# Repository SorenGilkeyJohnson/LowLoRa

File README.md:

# Low Power LoRa Weather Station

A solar powered, batteryless LoRa (expandable) sensor node powered from a supercapacitor charged by a small solar cell using an energy harvester. This was built around the Semtech SX1262 LoRa transceiver (US band; 915 MHz) and the low power MSPM0L110x MCU (TI; M0+), this board is a monitoring platform for anything you might want! The board is made around the solar cell and is roughly 23x24mm. 

## Overview

When researching this concept, I had found a few previous examples of this being done (e.g. [nootropicdesign](hackster.io/nootropicdesign/solar-powered-lora-weather-station-36b6ea)). I had not found an example, however, of a board that was fully self contained. When I was researching the component selection I really wanted it to be fully on board, which drove my decision to use a supercapacitor over a traditional Li-ION cell (almost none are SMD) and made me want to use a chip or PCB antenna. I found a supercapacitor that should work (this is my first time working with them), but I did not have enough room for an onboard antenna. Because of this I decided to add an external antenna through a connector. Another reason for this is the solar cell can block the RF waves from propagating properly. My project is still fairly unique from any existing solution, because I have found that it is rare to use a SMD solar cell. This is one of the biggest ones available on the market, as most are designed for handheld calculators. 
    Figuring out the power budget was very difficult for this project, and that was probably the thing I spent the most time on. Thankfully, the SX1262 datasheet had detailed power budget options, and I was able to base it off of that (almost all of my battery consumption should be from that). This project taught me a lot about the importance of component selection! (I probably spent 2 times longer on this than any other project I had done vs the routing). 
    When I get the board, I hope I can get it so that it is watertight. I have already done some research into gaskets for the humidity sensor (as this needs access to the outside world to get a good reading), but this seems pretty hard to do. There is a version of the sensor that has this built in, but it is far more expensive and is hard to get from most suppliers. I plan to use silicone around the PCB to protect the border of the solar cell from accidental damage, and put a piece of fiberglass over it. I made sure to keep all the parts that would petrude together, so I should have a slightly easier time designing the case. I hope I can get this board and test it out soon!

## Key Features

* **Ultra Low Power** This PCB should run at ultra low power, and may be able to run continuously in good sunlight (although it is designed for far less).
* **Small Board Size** The board for this is quite compact, and is mainly constrained by the size of the solar cell.
* **LoRa Transmit** This should be able to transfer over very long distances, and should be able to also extend range of other forming a "mesh"
* **Future expansion** Plentiful GPIO pins are broken out, so if one wanted to add more sensors, it would be as easy as soldering additional connectors to the PCB test pads.

## How It Works

1. The solar cell charges a supercapacitor through the BQ25504 energy harvesting IC, which is designed to extract power efficiently over a long period of time from very low amperage power sources. The datasheet mentioned being able to charge off of a piezoelectric element which would be way under the amount of current generated by a solar cell. Hopefully, this will overcome the natural discharge of the supercap.
2. A PMOS, switched by the MCU, gates power (VSYS) to the SX1262 and sensors, keeping the idle current as low as possible between transmissions because far less of the passive components are powered, and everything remains fully off.
3. The MSPM0L110x wakes periodically (very low sleep current ~<1uA; nothing compared to capacitor discharge), turns on the MOSFET to wake the sensors, reads the temperature/humidity and pressure sensors over I2C, and transmits the data over LoRa using the SX1262. Monitors the BAT_GOOD pin and turns everything off when it needs to!
4. The system was sized so that the supercapacitor can supply more than enough for the estimated ~15–30 mJ needed for a transmit burst. This part selection could be more conservative, but it was outside the range of ceramic capacitors, and there were not a lot of good low profile supercapacitor options.

## Hardware

| Main Components | Part | Notes |
| --- | --- | --- |
| LoRa Transceiver | SX1262 | Main IC, tuned for 915 MHz (US LoRa band) |
| Antenna | MMCX connector | External antenna due to PCB space constraints and having a metal backing (solar cell) |
| MCU | MSPM0L110x | I2C + SPI, wide voltage range, low cost, high availability from LCSC |
| Energy Harvester | BQ25504 | Manages charging from the solar cell and is very efficient. Gold standard for applications like this. |
| Solar Cell | KXOB121K04F-TR | very nice solar cell available on Digikey |
| Energy Storage | CXP-3R0335R-TW Supercapacitor | Low ESR; high capacitance; relatively space efficient |
| Load Switch | PMOS | Controlled by MCU to gate VSYS in order to save power for the rest of the system |
| Humidity/Temp Sensor | SHT4x | I2C |
| Pressure Sensor | LPS22HB | I2C |
| Antenna Switch | PE4259 | RF switch for the SX1262 (exact same component from reference design) |
| PCB Size | 23 mm x 25 mm | Large Solar Cell at a relatively high voltage compared to others on the market |

### 3D Renders

### PCB Layers

### PCB Layers

Schematic: [`Low Power LoRa Schematic.pdf`](https://www.google.com/search?q=images/Low%2520Power%2520LoRa%2520Schematic.pdf)

## Repository Structure

```
.
├── KiCAD/
│  ├── Low Power LoRa.kicad_pcb     # PCB layout
│  ├── Low Power LoRa.kicad_prl     # Project local settings
│  ├── Low Power LoRa.kicad_pro     # Project file
│  └── Low Power LoRa.kicad_sch     # Schematic
├── fabrication/
│  ├── bom.csv                      # Bill of materials
│  ├── gerbers.zip                  # Gerber files for PCB fabrication
│  └── pick_and_place.csv           # Pick-and-place file for assembly
├── images/
│  ├── Low Power LoRa Bottom View 3D.png
│  ├── Low Power LoRa Front View.png
│  ├── Low Power LoRa Layer 1.png
│  ├── Low Power LoRa Layer 2.png
│  ├── Low Power LoRa Layer 3.png
│  ├── Low Power LoRa Layer 4.png
│  └── Low Power LoRa Schematic.pdf
├── LICENSE
└── README.md

```

## Ordering the Board

Fabrication files can be found here: [`fabrication/`](https://www.google.com/search?q=fabrication/) folder:
The BOM was generated using LCSC, so ignore the minimum part quantities (these get messed up due to MOQ). You should be able to use the KiCAD files to generate your own.

## Programming

The MSPM0L110x is programmed with the SWD header. I do not have the board yet, so I will update this section more later when I have more information about real-world testing.

## Acknowledgments

* SX1262 RF matching network and BQ25504 based on respective companies reference design
* Review from r/PrintedCircuitBoard! (Thank you!)

## License

See [`LICENSE`](https://www.google.com/search?q=LICENSE) for details.

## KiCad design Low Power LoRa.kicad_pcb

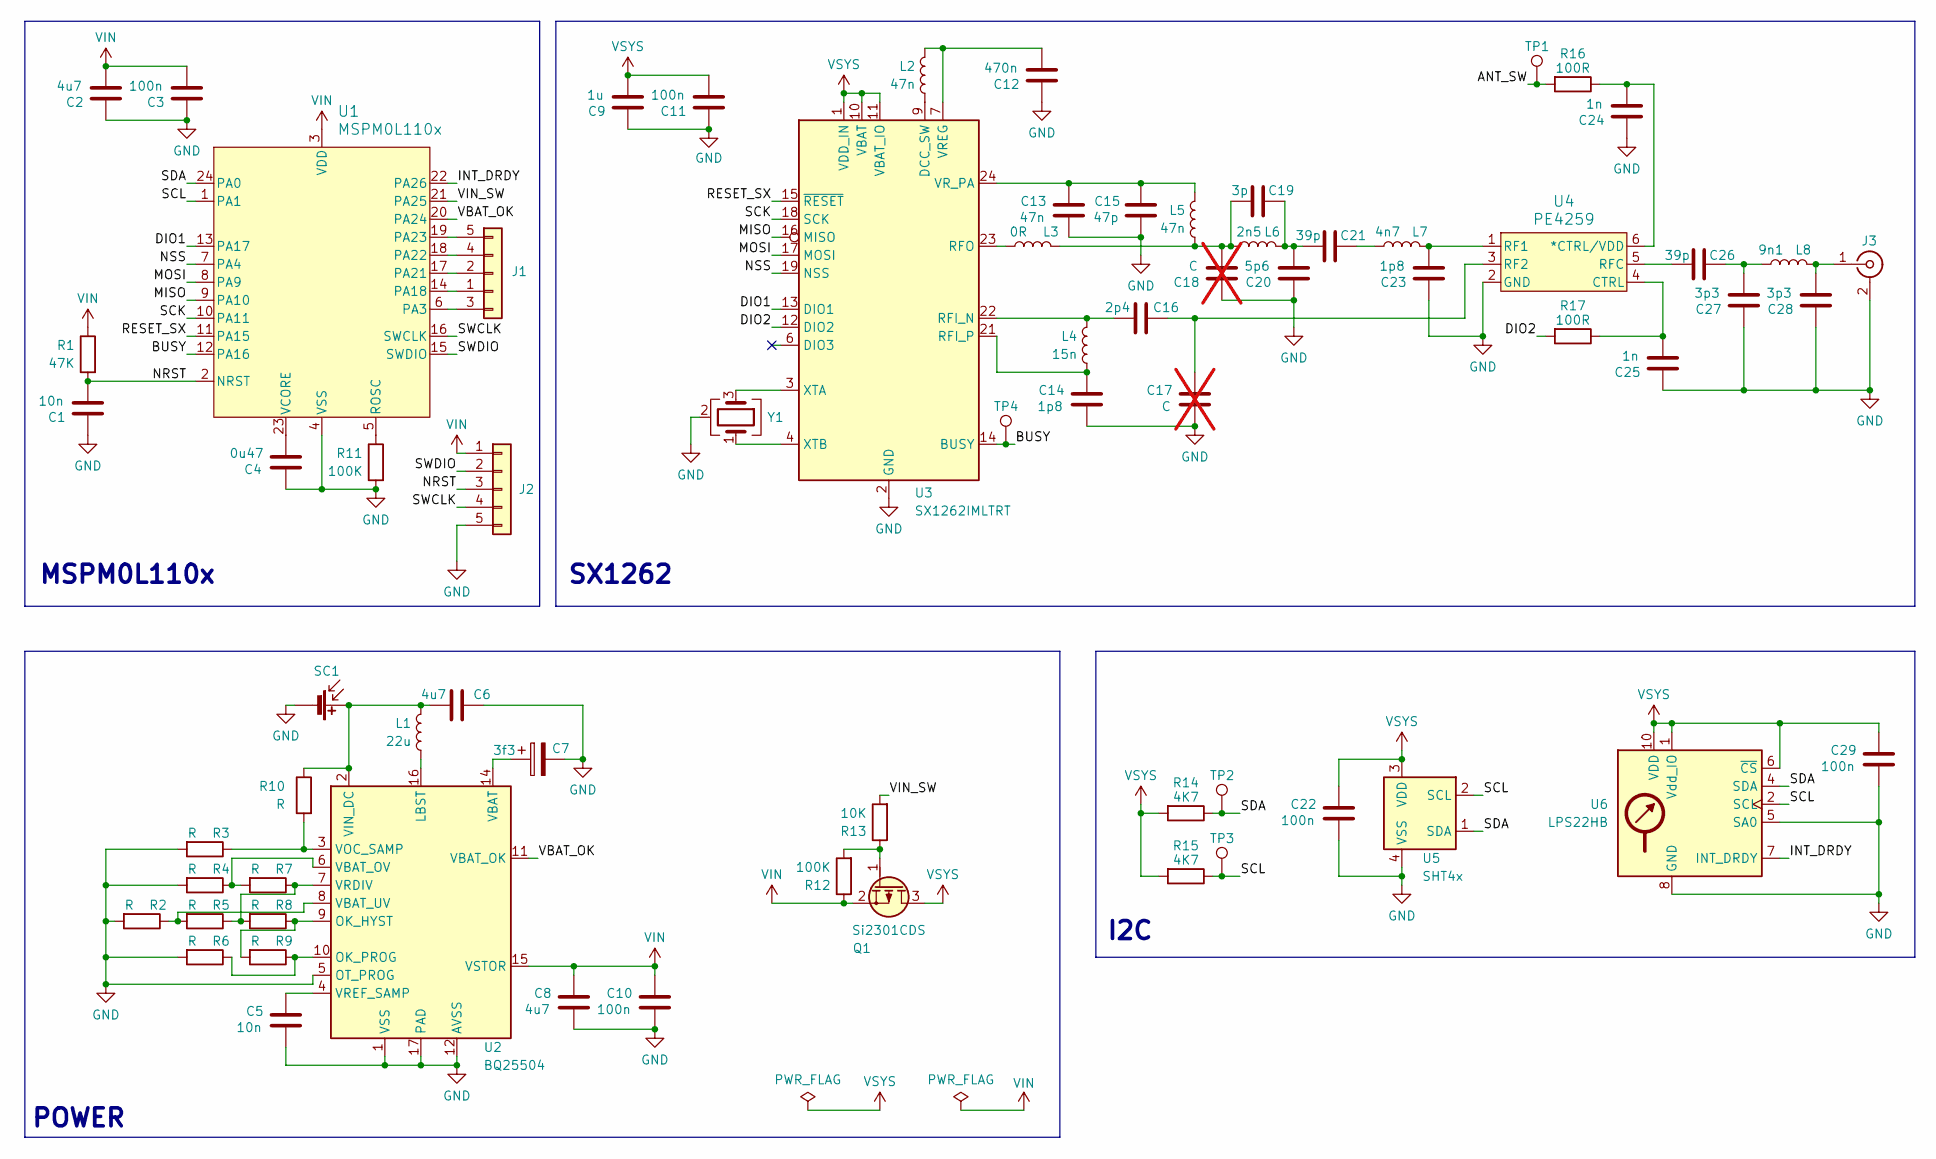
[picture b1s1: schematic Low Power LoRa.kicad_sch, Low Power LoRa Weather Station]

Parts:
C1, C5: 10n; C_0402_1005Metric
C2, C6, C8: 4u7; C_0402_1005Metric
C3, C10, C11, C22, C29: 100n; C_0402_1005Metric
C4: 0u47; C_0402_1005Metric
C7: 3f3; CP_Radial_D8.0mm_P3.50mm
C9: 1u; C_0402_1005Metric
C12: 470n; C_0402_1005Metric
C13: 47n; C_0402_1005Metric
C14, C23: 1p8; C_0402_1005Metric
C15: 47p; C_0402_1005Metric
C16: 2p4; C_0402_1005Metric
C17, C18: C; C_0402_1005Metric; not fitted
C19: 3p; C_0402_1005Metric
C20: 5p6; C_0402_1005Metric
C21, C26: 39p; C_0402_1005Metric
C24, C25: 1n; C_0402_1005Metric
C27, C28: 3p3; C_0402_1005Metric
J1: Conn_01x05; PinHeader_1x05_P1.27mm_Vertical_SMD_Pin1Left
J2: Conn_01x05; PinHeader_1x05_P1.27mm_Vertical
J3: Conn_Coaxial; MMCX_Molex_73415-1471_Vertical
L1: 22u; L_Wuerth_LQFS-3818
L2: 47n; L_0603_1608Metric
L3: 0R; L_0402_1005Metric
L4: 15n; L_0402_1005Metric
L5: 47n; L_0402_1005Metric
L6: 2n5; L_0402_1005Metric
L7: 4n7; L_0402_1005Metric
L8: 9n1; L_0402_1005Metric
Q1: Si2301CDS; SOT-23
R1: 47K; R_0402_1005Metric
R2, R3, R4, R5, R6, R7, R8, R9, R10: R; R_0402_1005Metric
R11, R12: 100K; R_0402_1005Metric
R13: 10K; R_0402_1005Metric
R14, R15: 4K7; R_0402_1005Metric
R16, R17: 100R; R_0402_1005Metric
SC1: KXOB121K04F-TR
TP1, TP2, TP3, TP4: TestPoint; TestPoint_Pad_D1.5mm
U1: MSPM0L110x; VQFN-24-1EP_4x4mm_P0.5mm_EP2.45x2.45mm_ThermalVias
U2: BQ25504; VQFN-16-1EP_3x3mm_P0.5mm_EP1.68x1.68mm_ThermalVias
U3: SX1262IMLTRT; QFN-24-1EP_4x4mm_P0.5mm_EP2.6x2.6mm
U4: PE4259; SOT-363_SC-70-6
U5: SHT4x; Sensirion_DFN-4_1.5x1.5mm_P0.8mm_SHT4x_NoCentralPad
U6: LPS22HB; ST_HLGA-10_2x2mm_P0.5mm_LayoutBorder3x2y
Y1: Crystal_GND24; Crystal_SMD_2016-4Pin_2.0x1.6mm

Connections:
/ANT_SW: R16.2, TP1.1 (1_1)
/BUSY: TP4.1 (1_1), U1.12 (PA16), U3.14 (BUSY)
/DIO1: U1.13 (PA17), U3.13 (DIO1)
/DIO2: R17.2, U3.12 (DIO2)
/INT_DRDY: U1.22 (PA26), U6.7 (INT_DRDY)
/MISO: U1.9 (PA10), U3.16 (MISO)
/MOSI: U1.8 (PA9), U3.17 (MOSI)
/NRST: C1.2, J2.3, R1.2, U1.2 (NRST)
/NSS: U1.7 (PA4), U3.19 (NSS)
/RESET_SX: U1.11 (PA15), U3.15 (~RESET)
/SCK: U1.10 (PA11), U3.18 (SCK)
/SCL: R15.1, TP3.1 (1_1), U1.1 (PA1), U5.2 (SCL), U6.2 (SCL)
/SDA: R14.1, TP2.1 (1_1), U1.24 (PA0), U5.1 (SDA), U6.4 (SDA)
/SWCLK: J2.4, U1.16 (SWCLK)
/SWDIO: J2.2, U1.15 (SWDIO)
/VBAT_OK: U1.20 (PA24), U2.11 (VBAT_OK)
/VIN_SW: R13.2, U1.21 (PA25)
GND: C1.1, C2.1, C3.1, C4.2, C5.2, C6.1, C7.2, C8.2, C9.1, C10.2, C11.1, C12.1, C13.2, C14.2, C15.2, C17.2, C18.1, C20.1, C22.2, C23.1, C24.1, C25.1, C27.1, C28.1, C29.2, J2.5, J3.2 (Ext), R2.2, R3.2, R4.2, R6.2, R11.2, SC1.2 (-), U1.4 (VSS), U1.25 (VSS), U2.1 (VSS), U2.5 (OT_PROG), U2.12 (AVSS), U2.13 (VSS), U2.17 (PAD), U3.2 (GND), U3.5 (GND), U3.8 (GND), U3.20 (GND), U3.25 (GND), U4.2 (GND), U5.4 (VSS), U6.3 (GND), U6.5 (SA0), U6.8 (GND), U6.9 (GND), Y1.2 (G), Y1.4 (G)
unnamed: C18.2, C19.2, L3.2, L5.2, L6.1
unnamed: C19.1, C20.2, C21.2, L6.2
unnamed: C21.1, L7.1
unnamed: C26.1, C27.2, L8.1
unnamed: J1.1, U1.14 (PA18)
unnamed: J1.2, U1.17 (PA21)
unnamed: J1.3, U1.6 (PA3)
unnamed: J1.4, U1.18 (PA22)
unnamed: J1.5, U1.19 (PA23)
unnamed: C28.2, J3.1 (In), L8.2
unnamed: Q1.1 (G), R12.2, R13.1
unnamed: C6.2, L1.1, R10.1, SC1.1 (+), U2.2 (VIN_DC)
unnamed: R11.1, U1.5 (ROSC)
unnamed: C4.1, U1.23 (VCORE)
unnamed: L1.2, U2.16 (LBST)
unnamed: R8.1, R9.2, U2.9 (OK_HYST)
unnamed: R6.1, R9.1, U2.10 (OK_PROG)
unnamed: C7.1, U2.14 (VBAT)
unnamed: R4.1, R7.2, U2.6 (VBAT_OV)
unnamed: R2.1, R5.2, U2.8 (VBAT_UV)
unnamed: R3.1, R10.2, U2.3 (VOC_SAMP)
unnamed: R5.1, R7.1, R8.2, U2.7 (VRDIV)
unnamed: C5.1, U2.4 (VREF_SAMP)
unnamed: L2.2, U3.9 (DCC_SW)
unnamed: C16.2, L4.1, U3.22 (RFI_N)
unnamed: C14.1, L4.2, U3.21 (RFI_P)
unnamed: L3.1, U3.23 (RFO)
unnamed: C12.2, L2.1, U3.7 (VREG)
unnamed: C13.1, C15.1, L5.1, U3.24 (VR_PA)
unnamed: U3.3 (XTA), Y1.3
unnamed: U3.4 (XTB), Y1.1
unnamed: C24.2, R16.1, U4.6 (*CTRL/VDD)
unnamed: C25.2, R17.1, U4.4 (CTRL)
unnamed: C23.2, L7.2, U4.1 (RF1)
unnamed: C16.1, C17.1, U4.3 (RF2)
unnamed: C26.2, U4.5 (RFC)
VIN: C2.2, C3.2, C8.1, C10.1, J2.1, Q1.2 (S), R1.1, R12.1, U1.3 (VDD), U2.15 (VSTOR)
VSYS: C9.2, C11.2, C22.1, C29.1, Q1.3 (D), R14.2, R15.2, U3.1 (VDD_IN), U3.10 (VBAT), U3.11 (VBAT_IO), U5.3 (VDD), U6.1 (Vdd_IO), U6.6 (~CS), U6.10 (VDD)

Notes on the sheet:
I2C
POWER
SX1262
MSPM0L110x

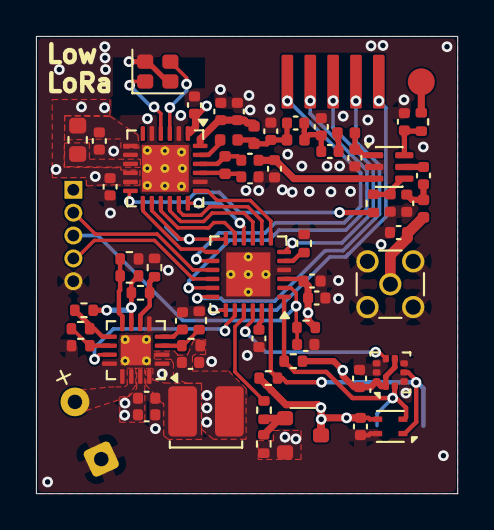
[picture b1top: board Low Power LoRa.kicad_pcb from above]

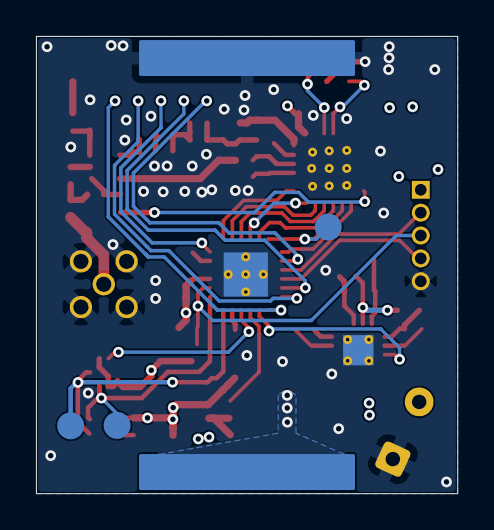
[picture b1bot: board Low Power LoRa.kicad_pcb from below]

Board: 4 copper layers, 23.4 x 25.4 mm, 70 parts (4 on the bottom side), 56 nets.

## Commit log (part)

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2026-06-25 Rename Low Power LoRa.kicad_pcb to KiCAD/Low Power LoRa.kicad_pcb
2026-06-25 Rename Low Power LoRa.kicad_prl to KiCAD/Low Power LoRa.kicad_prl
2026-06-25 Rename Low Power LoRa.kicad_pro to KiCAD/Low Power LoRa.kicad_pro
2026-06-25 Rename Low Power LoRa.kicad_sch to KiCAD/Low Power LoRa.kicad_sch
2026-06-27 Rename Low Power LoRa Schematic.pdf to images/Low Power LoRa Schematic.pdf
2026-06-27 Rename Low Power LoRa Layer 1.png to images/Low Power LoRa Layer 1.png
2026-06-27 Rename Low Power LoRa Layer 2.png to images/Low Power LoRa Layer 2.png
2026-06-27 Rename Low Power LoRa Layer 3.png to images/Low Power LoRa Layer 3.png
2026-06-27 Rename Low Power LoRa Layer 4.png to images/Low Power LoRa Layer 4.png
2026-06-27 Rename Low Power LoRa Bottom View 3D.png to images/Low Power LoRa Bottom View 3D.png
2026-06-27 Rename Low Power LoRa Front View.png to images/Low Power LoRa Front View.png
2026-06-27 Create LICENSE
2026-06-30 Rename Low Power LoRa_23.4x25.4mm_for_Default.zip to fabrication/gerbers.zip
2026-06-30 Rename Low Power LoRa.csv to bom.csv
2026-06-30 Rename Low Power LoRa-all-pos.csv to fabrication/pick_and_place.csv
2026-06-30 Rename bom.csv to fabrication/bom.csv
